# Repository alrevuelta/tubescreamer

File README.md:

# Description

This repository contains the schematics of a Tubescreamer like guitar pedal in EagleCad. This guitar pedal is a classical overdrive very well known among guitar players, specially in blues and rock style. It has several editions and modifications, such as TS-808, TS9 or TS10.

This schematics are based on the TS-808 edition, and the schematics found at gaussmarkov.net website.

# Features

Note that the hardware available at the `hw` folder, has been designed and routed trying to avoid complex wiring. For example, the potentiometers are soldered directly to the PCB, so no wiring is needed for them. Also, the LED can be soldered to the PCB directly without extra wiring. All other connections, such as 3DPDT and in/out TRS jacks, are disposed in an order that tries to avoid wires crossing, making it cleaner that in other designs.

The pedal can be used with a 9v battery or connected to a DC source at the same voltage. Note that the typical low pass filter is included.

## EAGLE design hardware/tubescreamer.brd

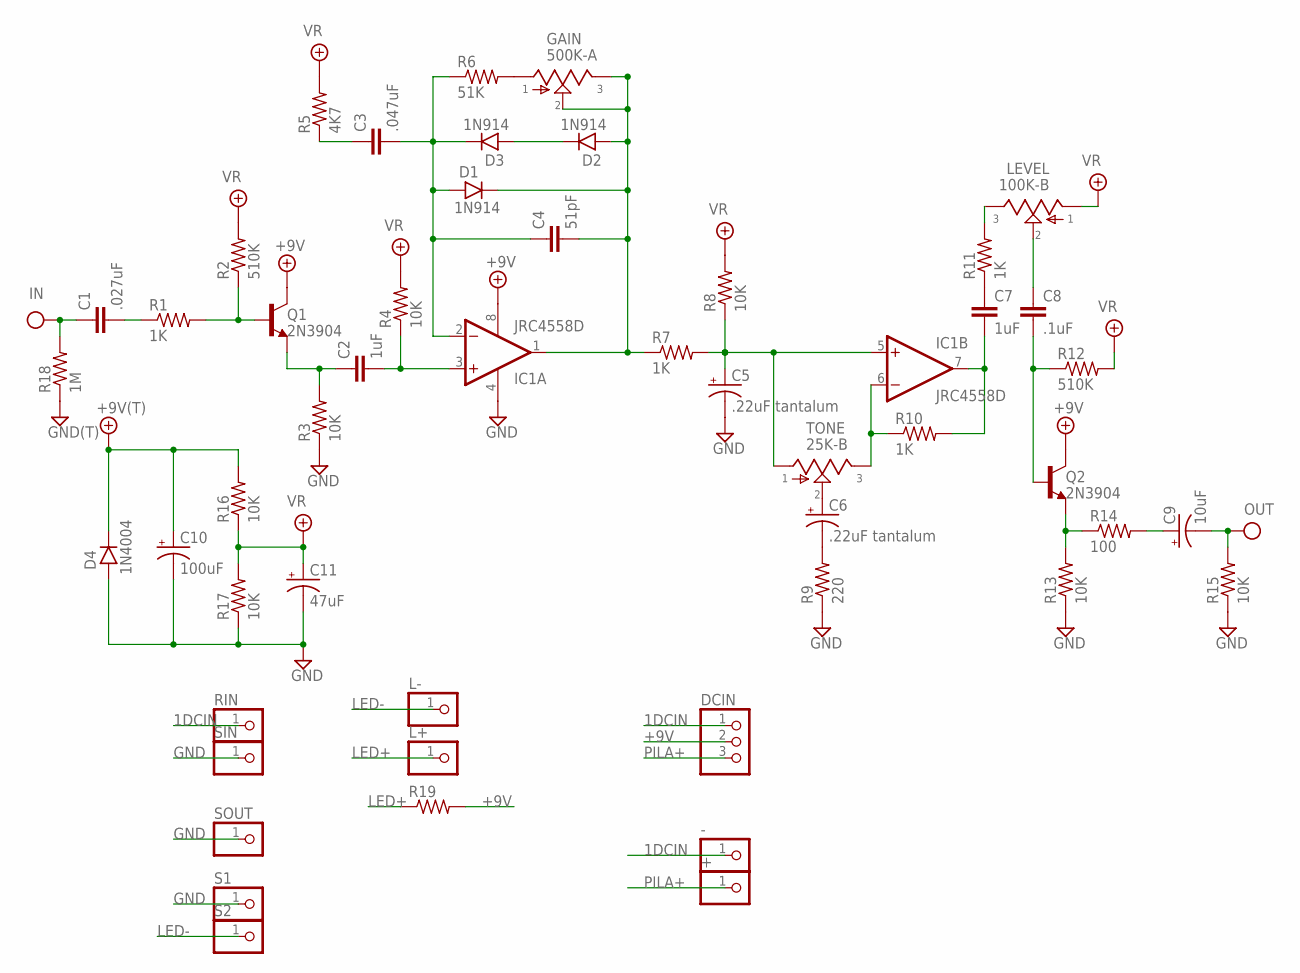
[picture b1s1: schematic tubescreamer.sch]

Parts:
+: PINHD-1X1CB; 1X01-CLEANBIG
+9V: +9V(T); PAD
-: PINHD-1X1CB; 1X01-CLEANBIG
C1: .027uF; 072X025
C2, C7: 1uF; 072X035
C3: .047uF; 072X025
C4: 51pF; 050X030_025_2
C5: .22uF tantalum; 044A_2
C6: .22uF tantalum; 044A
C8: .1uF; 072X025
C9: 10uF; 050_020_1
C10: 100uF; 063_025
C11: 47uF; 050_020_1
D1, D2, D3: 1N914; DO35-2
D4: 1N4004; DO41-3
DCIN: PINHD-1X3CB; 1X03-CLEANBIG
GAIN: 500K-A; POT
GND: GND(T); PAD
IC1: JRC4558D; DIL08
IN: IN(T); PAD
L+: PINHD-1X1CB; 1X01-CLEANBIG
L-: PINHD-1X1CB; 1X01-CLEANBIG
LEVEL: 100K-B; POT
OUT: OUT(T); PAD
Q1, Q2: 2N3904; TO92-
R1, R7, R10, R11: 1K; R0207/1V
R2, R12: 510K; R0207/1V
R3, R4, R8, R13, R15, R16, R17: 10K; R0207/1V
R5: 4K7; R0207/1V
R6: 51K; R0207/1V
R9: 220; R0207/1V
R14: 100; R0207/1V
R18: 1M; R0207/1V
R19: 6MM.1; R0207/1V
RIN: PINHD-1X1CB; 1X01-CLEANBIG
S1, S2: PINHD-1X1CB; 1X01-CLEANBIG
SIN: PINHD-1X1CB; 1X01-CLEANBIG
SOUT: PINHD-1X1CB; 1X01-CLEANBIG
TONE: 25K-B; POT

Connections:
1DCIN: -.1, DCIN.1, RIN.1
+9V: +9V.1, C10.+, D4.C, DCIN.2, IC1.8 (V+), Q1.1 (C), Q2.1 (C), R16.2, R19.2
GND: C5.2 (-), C10.-, C11.-, D4.A, GND.1, IC1.4 (V-), R3.1, R9.1, R13.1, R15.1, R17.1, R18.1, S1.1, SIN.1, SOUT.1
IN: C1.1, IN.1, R18.2
LED+: L+.1, R19.1
LED-: L-.1, S2.1
unnamed: GAIN.1, R6.2
unnamed: C1.2, R1.1
unnamed: Q1.2 (B), R1.2, R2.1
unnamed: C2.2, IC1.3 (+IN), R4.1
unnamed: C3.2, C4.1, D1.A, D3.C, IC1.2 (-IN), R6.1
unnamed: C2.1, Q1.3 (E), R3.2
unnamed: C4.2, D1.C, D2.A, GAIN.2, GAIN.3, IC1.1 (OUT), R7.1
unnamed: C6.1 (+), TONE.2
unnamed: C5.1 (+), IC1.5 (+IN), R7.2, R8.1, TONE.1
unnamed: IC1.6 (-IN), R10.1, TONE.3
unnamed: C3.1, R5.1
unnamed: C6.2 (-), R9.2
unnamed: C7.1, R11.1
unnamed: C7.2, IC1.7 (OUT), R10.2
unnamed: LEVEL.3, R11.2
unnamed: Q2.3 (E), R13.2, R14.1
unnamed: C8.1, LEVEL.2
unnamed: C8.2, Q2.2 (B), R12.1
unnamed: C9.+, R14.2
unnamed: D2.C, D3.A
OUT: C9.-, OUT.1, R15.2
PILA+: +.1, DCIN.3
VR: C11.+, LEVEL.1, R2.2, R4.2, R5.2, R8.2, R12.2, R16.1, R17.2

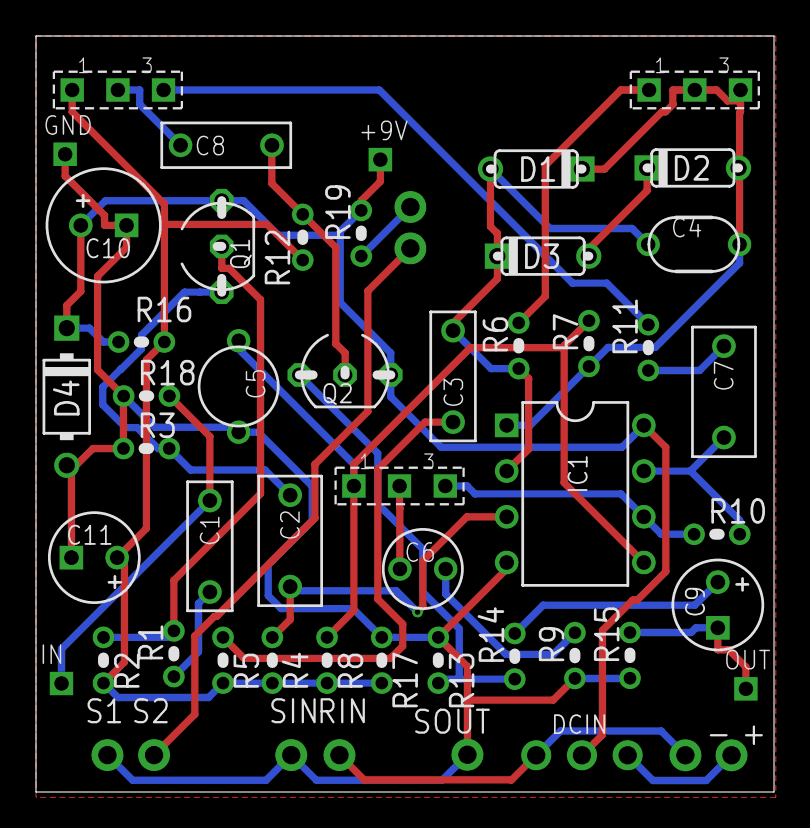
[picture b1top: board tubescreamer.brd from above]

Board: 2 copper layers, 41.0 x 42.0 mm, 54 parts (0 on the bottom side), 29 nets.
